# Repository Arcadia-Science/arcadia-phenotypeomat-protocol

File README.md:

# Arcadia-phenotypeomat-protocol

## Purpose

This repository contains the firmware and software necessary to aquire data with the Arcadia Phenotype-o-mat. The protocol for building the phenotype-o-mat is available [here](https://www.protocols.io/view/building-a-phenotype-o-mat-a-low-cost-diy-plate-re-yxmvm3r3ol3p/v1)

## Installation and Setup

This repository uses conda to manage software environments and installations. You can find operating system-specific instructions for installing miniconda [here](https://docs.conda.io/projects/miniconda/en/latest/). After installing conda, navigate to the directory in which you would like to clone the repository, and run the following commands to create the pipeline run environment.

```{bash}
git clone https://github.com/Arcadia-Science/arcadia-phenotypeomat-protocol.git
cd arcadia-phenotypeomat-protocol
conda env create -n phenotypeomat --file phenotypeomat.yml
conda activate phenotypeomat
```

This code also requires the Spinnaker SDK from Flir/Teledyne. The SDK and installation instructure are available [here](https://www.flir.com/products/spinnaker-sdk/?vertical=machine+vision&segment=iis).
Note, you must also install the Spinnaker python wheel appropriate for your version of Python and Spinnaker. These are also available through the link above.

To run the analysis apps, you must install additional dependencies.
```{bash}
conda env update -f apps_dependencies.yml
```

## Overview
### Phenotype-o-mat Control and Data Acquisition System

The Phenotype-o-mat system is an integrated solution for controlling experimental hardware and acquiring data, particularly designed for use with Blackfly cameras and Arduino-based control systems. This repository includes Arduino sketches for serial communication, a TOML configuration file for system settings, and Python modules for camera control and initialization.

## Components
### Arduino Sketches

- [serial_io.ino](./firmware_src/arduino_src/serial_io.ino): Implements basic serial I/O operations for Arduino, facilitating communication between the Arduino and a connected computer.

- [arduino_control_through_serial.ino](./firmware_src/arduino_src/arduino_control_through_serial.ino): An advanced sketch for controlling various Arduino outputs (e.g., LEDs, motors) through serial commands sent from a computer. This sketch is designed to work in tandem with the Python control scripts, allowing for automated hardware control during data acquisition.

### Configuration File

-  [phenotypeomat.toml](./flir_camera_tools/phenotypeomat.toml): A TOML file used to configure system parameters, such as device identifiers and operational settings. This file ensures that the system can be easily customized without modifying the source code.

### Python Modules

- [cam_tools.py](./flir_camera_tools/cam_tools.py): Provides a suite of tools for acquiring images from Blackfly cameras using the Spinnaker SDK. The script includes functions for barcode scanning, camera detection, image acquisition, resolution setting, and video saving.

### Setup

- Arduino Setup: Upload the appropriate .ino sketch to your Arduino device. Ensure that the Arduino is connected to your computer and that the correct port and baud rate are set.

- System Configuration: Edit the phenotypeomat.toml file to match your system's configuration. Specify device identifiers, operational parameters, and any other necessary settings.

- Python Environment: Ensure you have Python 3.9 or later installed. Install required dependencies, including OpenCV and PySpin (PySpin is part of the python wheel associated with the Spinnaker SDK), as well as any others needed by the scripts in this repository.

- Running the System: Use the Python scripts to control the system. The scripts will communicate with the Arduino through serial commands and control the cameras based on the settings specified in the TOML file.

### Physical components
All 3d printable physical components of the phenotype-o-mat are available [here](https://www.shapeways.com/designer/ben_arcadia/lists/phenotype-o-mat)
The printed circuit board can be ordered from [here](https://oshpark.com/shared_projects/38DzJZmF)
All design files are in this repository in the [design_files/](design_files/) folder.

### Usage
#### Data Acquisition

- Start the Python assay script (e.g., test_assay_growth_curve_chlamy.py) to initiate the data acquisition process. The script will interact with the Arduino to control the experimental setup and use the camera tools to acquire and save images or videos.

### Tools for writing data aquisition scripts
#### Illumination hardware Control
 Currently, the Arduino code allows control of 5 illumination sources: white lite trans-illumination and incident light at 4 wavelengths: 460nm, 535nm, 590nm, and 670nm. Control of the Arduino is mediated by a generic serial communication system to facilitate the addition of other functionality. The assay scripts communicate with the arduino through use of the [pySerial](https://pyserial.readthedocs.io/en/latest/shortintro.html) module. The Arduino sketches can be modified to add or change hardware control functionalities. Refer to the comments within each sketch for guidance on customization. The current usage is outlined below.

 After initializing a serial connection with the arduino (see example assay or pySerial documentation to accomplish this) commands can be sent in the following format:

- ```GET LED_[WAVELENGTH]_STATUS;``` where wavelength is 460, 535, 590, 670, or TRANS.  e.g. GET LED_460_STATUS; will return a 0 (LED is on) or a 1 (LED is off).
- ```SET LED_[WAVELENGTH]_STATUS [desired numerical status];``` Where wavelength is 460, 535, 590, 670, or TRANS. And 'desired numerical status is either 0 (turn on LED) or 1 (turn off LED  e.g. SET LED_460_STATUS 0; will turn on the 460nm LED.
- ```GET_AND_SET LED_[WAVELENGTH]_STATUS [desired numerical status];``` Where wavelength is 460, 535, 590, 670, or TRANS. And 'desired numerical status is either 0 (turn on LED) or 1 (turn off LED  e.g. GET_AND_SET LED_460_STATUS 1;``` Will attempt to turn off the 460 LED and then check the LED status and return the current status.  This is helpful to be sure the SET command changed the LED status.

##### Barcode Reading

- ``` bcode_read()```: Invoke this function to read barcodes using a USB handheld scanner. It prompts for a barcode scan and returns the scanned code.

##### Camera control
###### Several of these functions are part of the Spinnaker SDK and we direct you to the SDK documentation for more information.  They are provided here because these are the minimum functions required to interface with the camera.  For example usage see the provded 'test_assay.'

- ```detect_cams(n=None)```: Detects the number of connected cameras. Optionally, specify the number of expected cameras with n.
- ```ps.System.GetInstance()```: Initializes an object to interface between the computer system and the PySpin SDK.
- ```system.GetCameras()```: Property of a system object that queries the computer system USB and GigE interfaces for Blackfly cameras and returns handles for those cameras in a list.
- ```system.ReleaseInstance()```: Property of a system object that stops that instance.
- ```cam_list.Clear()```: Property of a camera list that ends the handlers for those cameras and returns the cameras to a idle state.
- ```camera.Init()```: Initializes a camera object. Camera objects can be de-initialized and returned to idle state by calling '''del camera'''

##### Image Acquisition and Processing

- ```get_save(cam, wl, device, barcode, delay=None)```: Acquires an image from the camera after a specified delay and saves it. The function turns on specified illumination, captures the frame, and then turns the illumination off.
- ```grab_images(cam)```: Captures images from the specified camera and returns them along with timestamps.
- ```set_resolution(cam, x_dim, y_dim)```: Sets the dimensions of the acquired image. X and Y dim should be in pixels. `cam` is a camera object.
- ```set_binning(can, x_dim, y_dim)```: Sets the dimensions of binning. X and Y dim should be in pixels. `cam` is a camera object.
- ```set_gain_mode(cam, mode="once")```: Sets the automatic gain mode of the camera.  Mode should be `once`, `continuous`, or `off`.
- ```get_gain_mode(cam)```: Returns the current automatic gain mode setting from the camera.
- ```set_expos_mode(cam, mode="once")```: Sets the automatic exposure mode of the camera.  Mode should be once, continuous, or off.
- ```set_expos_time(cam, time)```: Sets a custom exposure time.  Expects values in micro seconds.
- ```get_auto_exposure(cam)```: Returns the current autoexposure value determined by the camera in micro seconds.
- ```set_framerate(cam, frame_rate=None)```: sets the framerate set on the camera. `frame_rate` should be in hz.
- ```get_framerate(cam)```: Returns the current framerate on the camera.

##### Video Saving

- ```save_avi(images, frame_rate=None, barcode=None, prefix=None, path=None, is_color=None)```: Saves a sequence of images as an AVI file using OpenCV.
- ```save_video(images, frame_rate=None, barcode=None, prefix=None, path=None)```: Saves a list of images as a video file using the Spinnaker SDK.

### Description of the folder structure

[design_files/](design_files/) Contains design files for the components of the phenotype-o-mat including the printed circuit board. \
[flir_camera_tools/](flir_camera_tools/) Contains the python module to interact with the phenotype-o-mat. \
[firmware_src/](firmware_src/) Contains the firmware to be uploaded to the Arduino which operates the illumination system. \
[test_assay_growth_curve_chlamy.py](test_assay_growth_curve_chlamy.py) Is an example assay for aquiring data from the phenotype-o-mat.  It uses much of the currently implemented functionality. 

### Compute Specifications

- Any system with a >=  USB 3.0 High Speed bus.  USB 3.0 Super Speed or better is preferred.

## Contributing

See how we recognize [feedback and contributions to our code](https://github.com/Arcadia-Science/arcadia-software-handbook/blob/main/guides-and-standards/guide-credit-for-contributions.md).

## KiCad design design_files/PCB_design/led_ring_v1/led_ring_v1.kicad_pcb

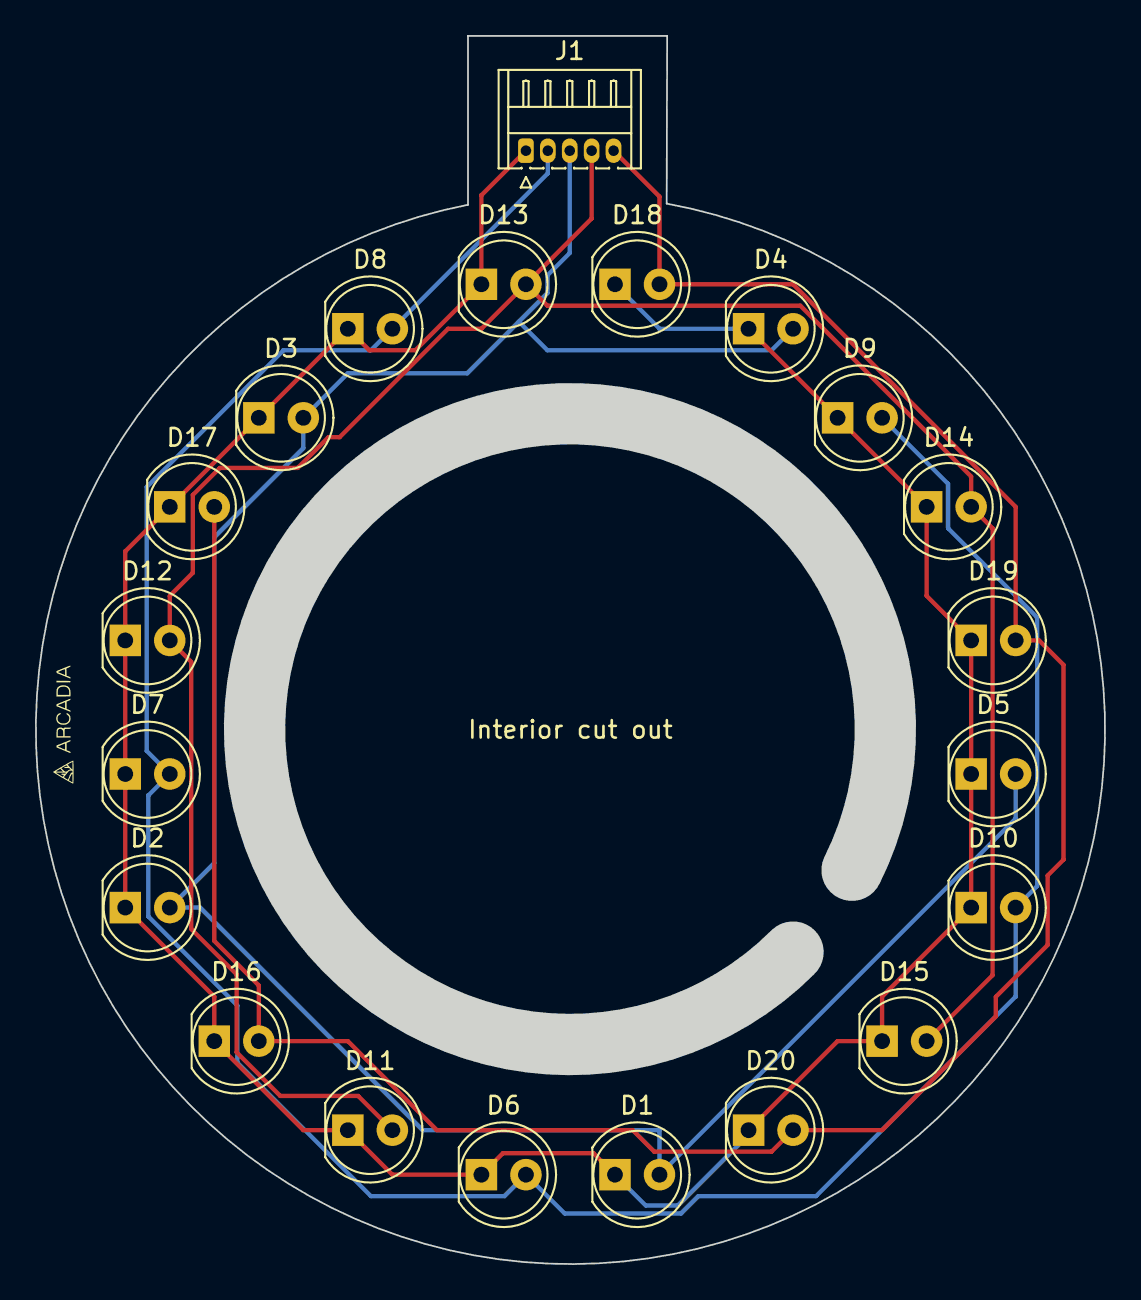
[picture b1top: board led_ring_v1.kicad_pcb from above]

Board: 2 copper layers, 61.0 x 70.1 mm, 21 parts (0 on the bottom side), 5 nets.

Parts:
D1, D2, D3, D4, D5: LED_blue; LED_D5.0mm
D6, D7, D8, D9, D10: LED_green; LED_D5.0mm
D11, D12, D13, D14, D15: LED_yellow; LED_D5.0mm
D16, D17, D18, D19, D20: LED_red; LED_D5.0mm
J1: Conn_01x05_Male; Hirose_DF13-05P-1.25DS_1x05_P1.25mm_Horizontal

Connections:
unnamed: D1.1 (K), D2.1 (K), D3.1 (K), D4.1 (K), D5.1 (K), D6.1 (K), D7.1 (K), D8.1 (K), D9.1 (K), D10.1 (K), D11.1 (K), D12.1 (K), D13.1 (K), D14.1 (K), D15.1 (K), D16.1 (K), D17.1 (K), D18.1 (K), D19.1 (K), D20.1 (K), J1.1
unnamed: D1.2 (A), D2.2 (A), D3.2 (A), D4.2 (A), D5.2 (A), J1.3
unnamed: D6.2 (A), D7.2 (A), D8.2 (A), D9.2 (A), D10.2 (A), J1.2
unnamed: D11.2 (A), D12.2 (A), D13.2 (A), D14.2 (A), D15.2 (A), J1.4
unnamed: D16.2 (A), D17.2 (A), D18.2 (A), D19.2 (A), D20.2 (A), J1.5

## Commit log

2024-03-05 adding a folder for the design files
2024-03-05 Adding the firmware. Currently this is only arduino source code for the light ring.
2024-03-05 Adding software for interfacing with flir/spinnaker SDK cameras.
2024-03-05 Added .stl files via upload
    All of the CAD files for 3D printing phenotype-o-mat parts
2024-03-05 Linted all code
2024-03-07 removed extra lines from serial_ino.ino
2024-03-07 expanded the description of what serial_ino does
2024-03-07 added chlamy growth curve assay
2024-03-08 linting of test_assay_growth_curve_chlamy.py
2024-03-08 added statement about how many PTOmats can be connected for the example script to run.
2024-03-08 fixed line length issue in example script
2024-03-08 removed 2 instances of trailing white spaces from test_assay
2024-03-13 initial commit of new README file. Also added the yml file for conda management and made changes to the phenotypeomat.toml file to bring it up to date WRT dependencies and naming
2024-03-14 added file structure, description of many camera control functions and description of how to interface with the arduino to the README
2024-03-14 formatting changes to README
2024-03-15 added package version and cleaned up .yml
2024-03-15 added shapeways link for printable components and made the components header appear as a header
2024-03-15 double checked .yml file and made small formatting changes to README
2024-04-16 Added a link to Osh park to the readme
2024-09-19 solid implementation of colony segmentation
2024-09-20 Working demo for segmenting colonies
2024-09-24 finish demo
2024-09-24 Update README.md
    add install directions to README
2024-09-24 Update README.md
    more install directions
